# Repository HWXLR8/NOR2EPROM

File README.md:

# NOR2EPROM
This is a "simple" drop in replacement for 27C322 UV EPROMs which uses an MX29LV320 (or pin-compatible) NOR flash.
Address lines are shifted from 5V -> 3.3V using 3x 74LVC245 and data lines are shifted from 3.3V -> 5V using 2x 74HCT245.

### Schematic

### PCB

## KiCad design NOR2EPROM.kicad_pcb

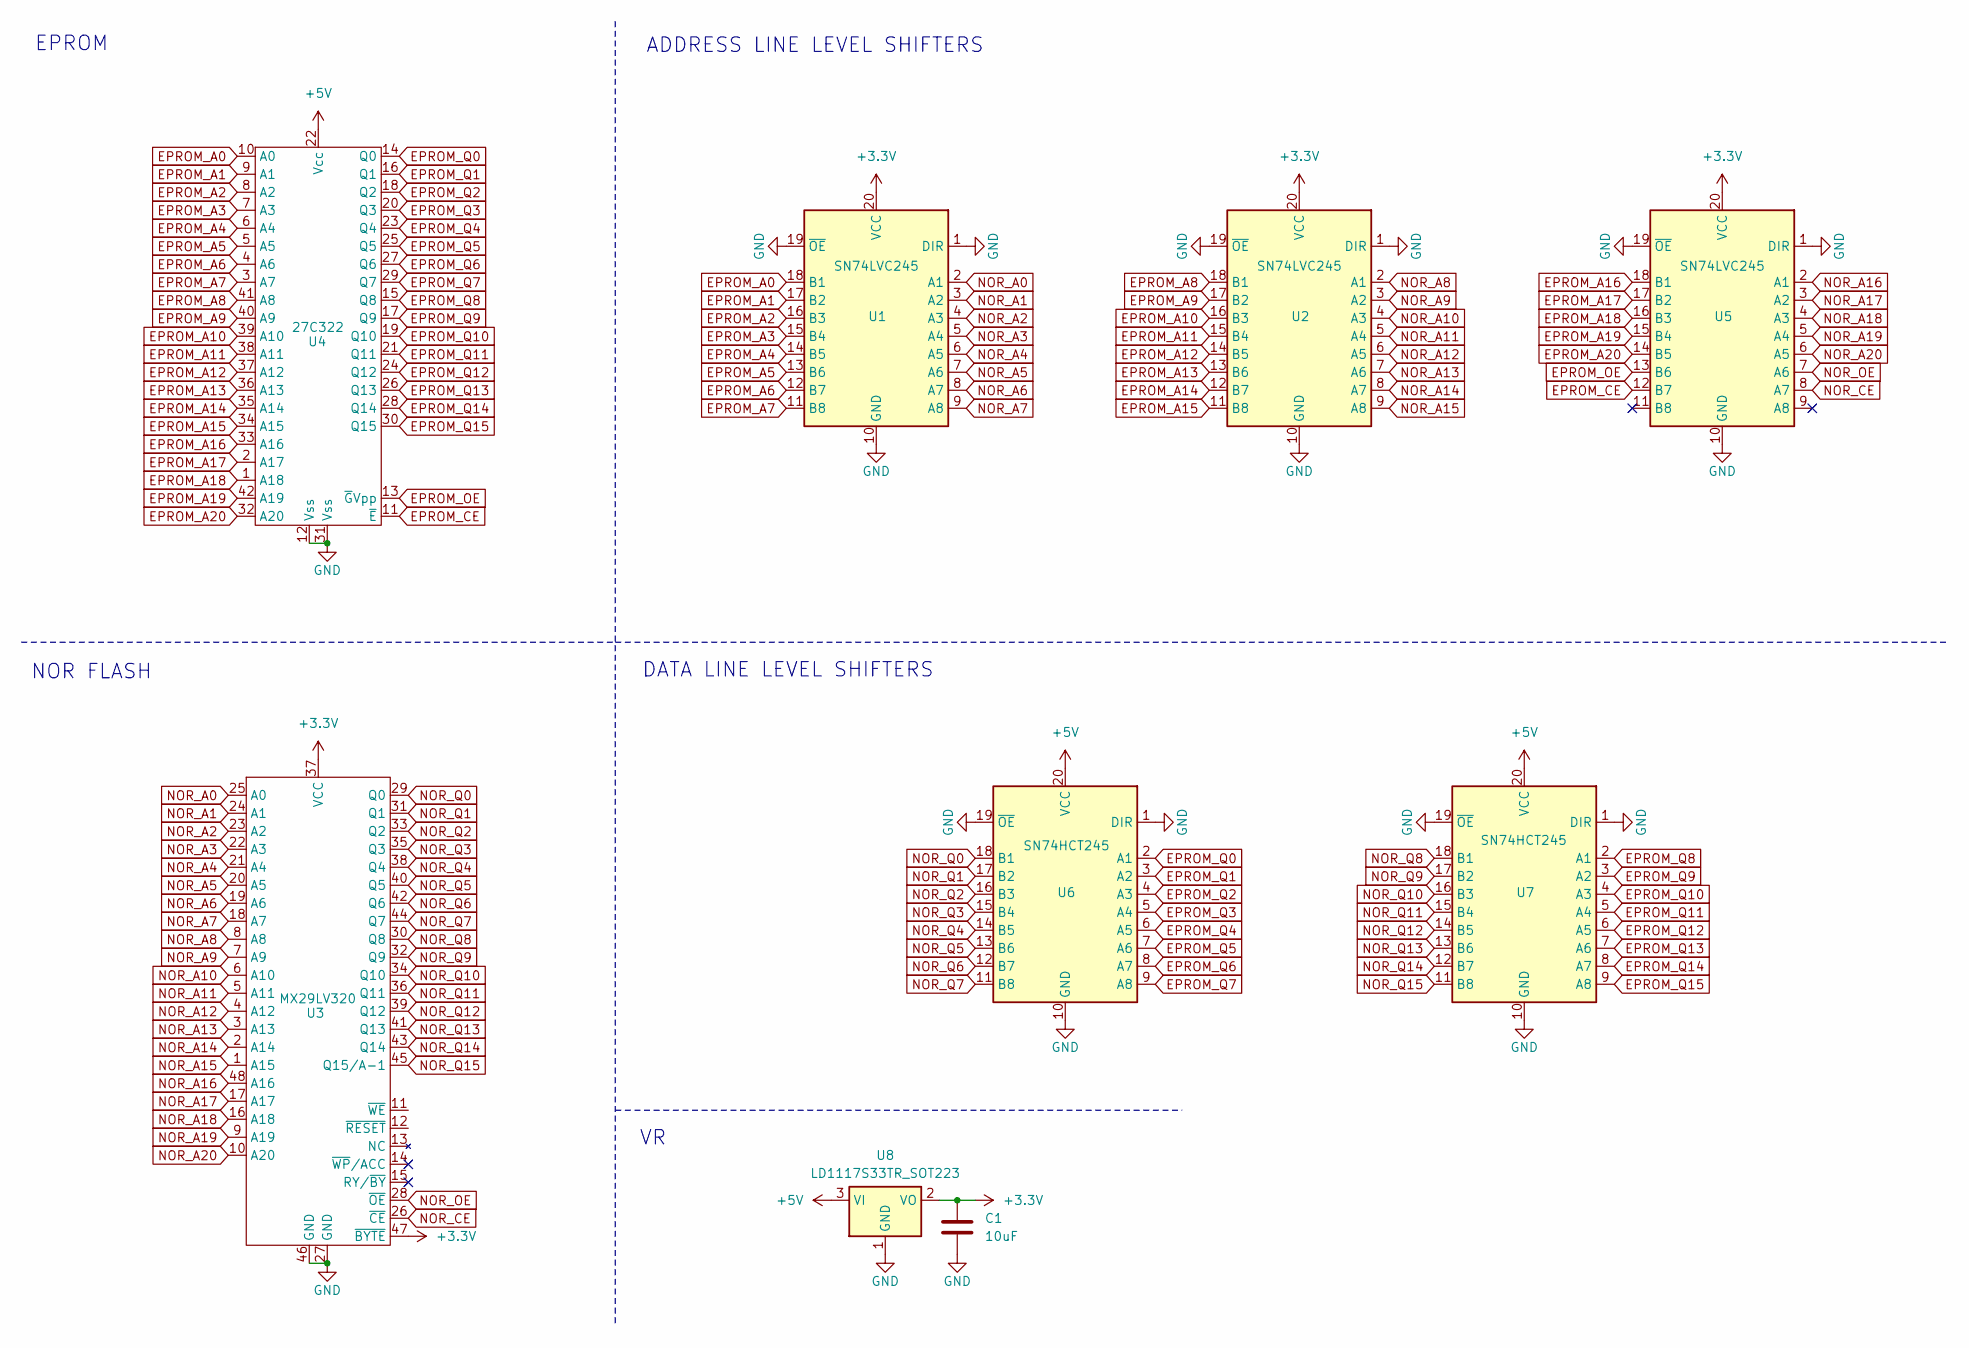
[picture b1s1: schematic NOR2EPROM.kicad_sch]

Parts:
C1: 10uF; C_0805_2012Metric
U1, U2, U5: SN74LVC245; TSSOP-20_4.4x6.5mm_P0.65mm
U3: MX29LV320; TSOP-I-48_18.4x12mm_P0.5mm
U4: 27C322; DIP-42_W15.24mm
U6, U7: SN74HCT245; TSSOP-20_4.4x6.5mm_P0.65mm
U8: LD1117S33TR_SOT223; SOT-223-3_TabPin2

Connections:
+3.3V: C1.1, U1.20 (VCC), U2.20 (VCC), U3.37 (VCC), U3.47 (~BYTE), U5.20 (VCC), U8.2 (VO)
+5V: U4.22 (Vcc), U6.20 (VCC), U7.20 (VCC), U8.3 (VI)
EPROM_A0: U1.18 (B1), U4.10 (A0)
EPROM_A1: U1.17 (B2), U4.9 (A1)
EPROM_A2: U1.16 (B3), U4.8 (A2)
EPROM_A3: U1.15 (B4), U4.7 (A3)
EPROM_A4: U1.14 (B5), U4.6 (A4)
EPROM_A5: U1.13 (B6), U4.5 (A5)
EPROM_A6: U1.12 (B7), U4.4 (A6)
EPROM_A7: U1.11 (B8), U4.3 (A7)
EPROM_A8: U2.18 (B1), U4.41 (A8)
EPROM_A9: U2.17 (B2), U4.40 (A9)
EPROM_A10: U2.16 (B3), U4.39 (A10)
EPROM_A11: U2.15 (B4), U4.38 (A11)
EPROM_A12: U2.14 (B5), U4.37 (A12)
EPROM_A13: U2.13 (B6), U4.36 (A13)
EPROM_A14: U2.12 (B7), U4.35 (A14)
EPROM_A15: U2.11 (B8), U4.34 (A15)
EPROM_A16: U4.33 (A16), U5.18 (B1)
EPROM_A17: U4.2 (A17), U5.17 (B2)
EPROM_A18: U4.1 (A18), U5.16 (B3)
EPROM_A19: U4.42 (A19), U5.15 (B4)
EPROM_A20: U4.32 (A20), U5.14 (B5)
EPROM_CE: U4.11 (~E), U5.12 (B7)
EPROM_OE: U4.13 (~GVpp), U5.13 (B6)
EPROM_Q0: U4.14 (Q0), U6.2 (A1)
EPROM_Q1: U4.16 (Q1), U6.3 (A2)
EPROM_Q2: U4.18 (Q2), U6.4 (A3)
EPROM_Q3: U4.20 (Q3), U6.5 (A4)
EPROM_Q4: U4.23 (Q4), U6.6 (A5)
EPROM_Q5: U4.25 (Q5), U6.7 (A6)
EPROM_Q6: U4.27 (Q6), U6.8 (A7)
EPROM_Q7: U4.29 (Q7), U6.9 (A8)
EPROM_Q8: U4.15 (Q8), U7.2 (A1)
EPROM_Q9: U4.17 (Q9), U7.3 (A2)
EPROM_Q10: U4.19 (Q10), U7.4 (A3)
EPROM_Q11: U4.21 (Q11), U7.5 (A4)
EPROM_Q12: U4.24 (Q12), U7.6 (A5)
EPROM_Q13: U4.26 (Q13), U7.7 (A6)
EPROM_Q14: U4.28 (Q14), U7.8 (A7)
EPROM_Q15: U4.30 (Q15), U7.9 (A8)
GND: C1.2, U1.1 (DIR), U1.10 (GND), U1.19 (~OE), U2.1 (DIR), U2.10 (GND), U2.19 (~OE), U3.27 (GND), U3.46 (GND), U4.12 (Vss), U4.31 (Vss), U5.1 (DIR), U5.10 (GND), U5.19 (~OE), U6.1 (DIR), U6.10 (GND), U6.19 (~OE), U7.1 (DIR), U7.10 (GND), U7.19 (~OE), U8.1 (GND)
NOR_A0: U1.2 (A1), U3.25 (A0)
NOR_A1: U1.3 (A2), U3.24 (A1)
NOR_A2: U1.4 (A3), U3.23 (A2)
NOR_A3: U1.5 (A4), U3.22 (A3)
NOR_A4: U1.6 (A5), U3.21 (A4)
NOR_A5: U1.7 (A6), U3.20 (A5)
NOR_A6: U1.8 (A7), U3.19 (A6)
NOR_A7: U1.9 (A8), U3.18 (A7)
NOR_A8: U2.2 (A1), U3.8 (A8)
NOR_A9: U2.3 (A2), U3.7 (A9)
NOR_A10: U2.4 (A3), U3.6 (A10)
NOR_A11: U2.5 (A4), U3.5 (A11)
NOR_A12: U2.6 (A5), U3.4 (A12)
NOR_A13: U2.7 (A6), U3.3 (A13)
NOR_A14: U2.8 (A7), U3.2 (A14)
NOR_A15: U2.9 (A8), U3.1 (A15)
NOR_A16: U3.48 (A16), U5.2 (A1)
NOR_A17: U3.17 (A17), U5.3 (A2)
NOR_A18: U3.16 (A18), U5.4 (A3)
NOR_A19: U3.9 (A19), U5.5 (A4)
NOR_A20: U3.10 (A20), U5.6 (A5)
NOR_CE: U3.26 (~CE), U5.8 (A7)
NOR_OE: U3.28 (~OE), U5.7 (A6)
NOR_Q0: U3.29 (Q0), U6.18 (B1)
NOR_Q1: U3.31 (Q1), U6.17 (B2)
NOR_Q2: U3.33 (Q2), U6.16 (B3)
NOR_Q3: U3.35 (Q3), U6.15 (B4)
NOR_Q4: U3.38 (Q4), U6.14 (B5)
NOR_Q5: U3.40 (Q5), U6.13 (B6)
NOR_Q6: U3.42 (Q6), U6.12 (B7)
NOR_Q7: U3.44 (Q7), U6.11 (B8)
NOR_Q8: U3.30 (Q8), U7.18 (B1)
NOR_Q9: U3.32 (Q9), U7.17 (B2)
NOR_Q10: U3.34 (Q10), U7.16 (B3)
NOR_Q11: U3.36 (Q11), U7.15 (B4)
NOR_Q12: U3.39 (Q12), U7.14 (B5)
NOR_Q13: U3.41 (Q13), U7.13 (B6)
NOR_Q14: U3.43 (Q14), U7.12 (B7)
NOR_Q15: U3.45 (Q15/A-1), U7.11 (B8)

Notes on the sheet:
EPROM
ADDRESS LINE LEVEL SHIFTERS
NOR FLASH
DATA LINE LEVEL SHIFTERS

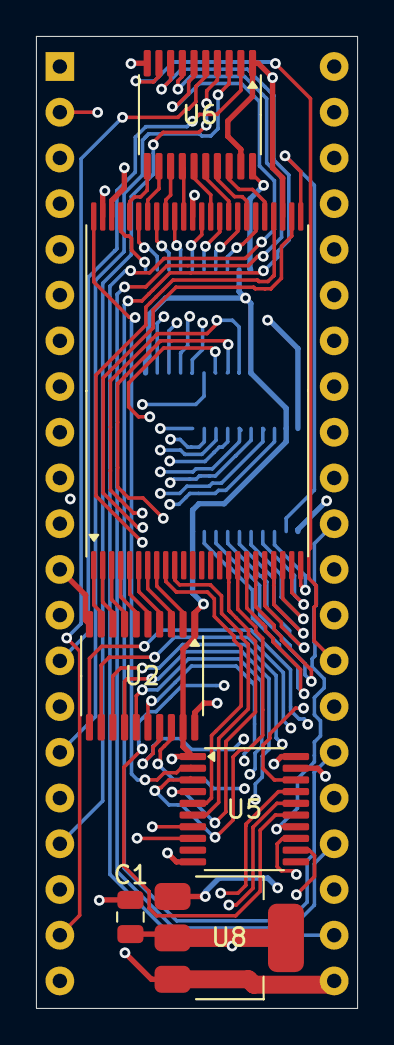
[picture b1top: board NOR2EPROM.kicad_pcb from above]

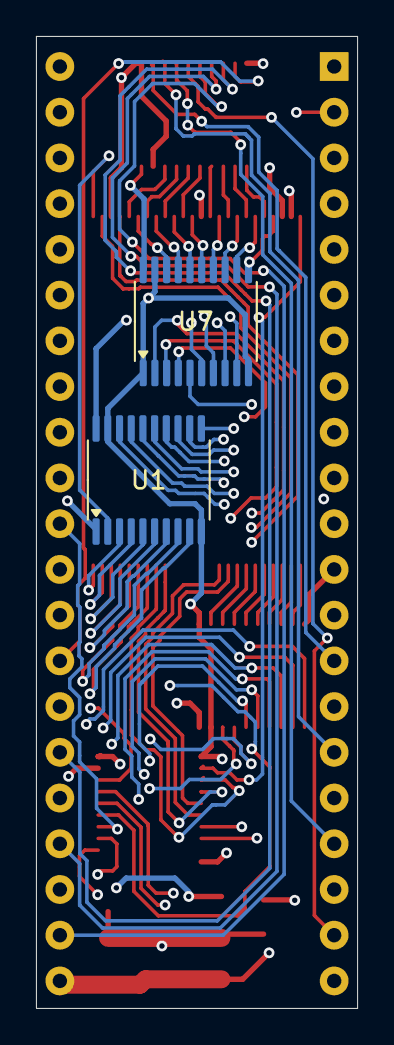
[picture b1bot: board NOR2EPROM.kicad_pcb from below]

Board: 4 copper layers, 17.8 x 54.0 mm, 9 parts (2 on the bottom side), 81 nets.

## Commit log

2024-12-19 init
2024-12-20 finalize alpha schematic done
2024-12-21 add output cap, position components before routing
2024-12-21 routing checkpoint
2024-12-24 finished routing
2024-12-24 fix drc errors
2024-12-25 clean up schematic
2024-12-25 add pcb pics
2024-12-25 add README
2024-12-27 level shift OE and CE lines
